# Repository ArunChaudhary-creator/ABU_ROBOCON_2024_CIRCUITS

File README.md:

# ABU_ROBOCON_2024_CIRCUITS
ABU_Robocon_2024 necessary circuits

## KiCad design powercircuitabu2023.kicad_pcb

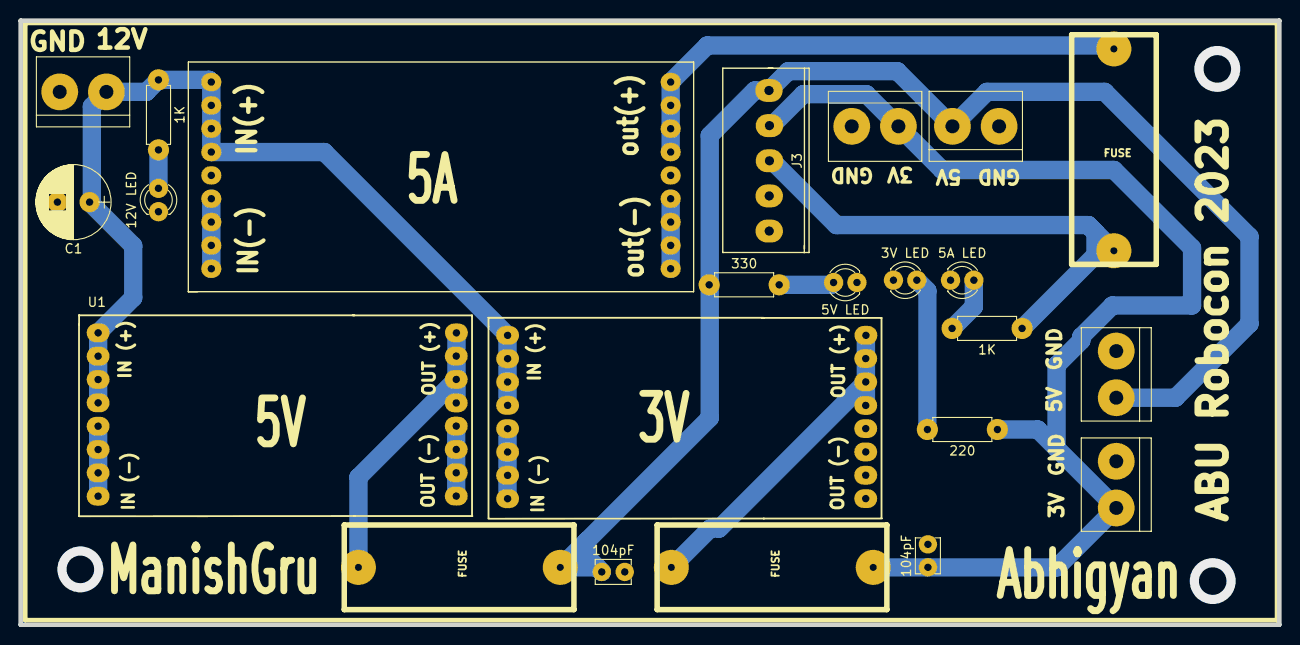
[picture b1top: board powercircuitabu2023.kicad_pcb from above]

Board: 2 copper layers, 137.0 x 65.8 mm, 23 parts (0 on the bottom side), 12 nets.

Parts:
1K, 1K#2: 1k; Resistor_small
3V LED, 5A LED, 5V LED, 12V LED: LED; LED_D3.0mm
104pF: 104pF; Capacitor_Disc_Small
104pF#2: 104pf; Capacitor_Disc_Small
220: 220; Resistor_small
330: 330; Resistor_small
C1: 100uF; Capacitor_100uF
F1, F2, F3: FUSE; Fuse_Holder
J1, J2, J4, J5, J6: Bournier; bornier2
J3: 4 pin JST; JST_5_BIG
U1: 5V; Buck_Regulator
U2: 3V; Buck_Regulator
U3: 5A Buck; Buck_5A

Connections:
12V: 1K.1, C1.1, J1.2, U1.1 (IN(+)), U2.1 (IN(+)), U3.1 (IN(+))
B3V: 104pF.1, 220.1, F2.2, J3.2, J5.1, J6.1
B5A: 1K#2.1, F3.2, J3.3
B5V: 104pF#2.1, 330.1, F1.2, J2.1, J3.1, J4.1
GND: 3V LED.1 (K), 5A LED.1 (K), 5V LED.1 (K), 12V LED.1 (K), 104pF.2, 104pF#2.2, C1.2, J1.1, J2.2, J3.4, J4.2, J5.2, J6.2, U1.2 (IN(-)), U1.4 (OUT(-)), U2.2 (IN(-)), U2.4 (OUT(-)), U3.2 (IN(-)), U3.4 (OUT(-))
unnamed: 1K.2, 12V LED.2 (A)
unnamed: 3V LED.2 (A), 220.2
unnamed: 1K#2.2, 5A LED.2 (A)
unnamed: 5V LED.2 (A), 330.2
unnamed: F1.1, U1.3 (OUT(+))
unnamed: F2.1, U2.3 (OUT(+))
unnamed: F3.1, U3.3 (OUT(+))

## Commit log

2025-06-16 some kicad circuits files are uploaded.
2025-06-16 pdf files of circuits
